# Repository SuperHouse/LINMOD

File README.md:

LINbus interface module
=======================
Copyright 2017 SuperHouse Automation Pty Ltd  www.superhouse.tv  

Simple serial interface breakout for LINbus. Includes an RJ45 connector
with the same pinout as AXA electric window motors.

Features:

 * MCP2003 LIN driver
 * Serial header matching FTDI pinout
 * RJ45 socket for LIN connection
 * DC jack to supply LINbus power

More information:

  http://www.superhouse.tv/linmod

INSTALLATION
------------
The design is saved as an EAGLE project. EAGLE PCB design software is
available from www.cadsoftusa.com free for non-commercial use. To use
this project download it and place the directory containing these files
into the "eagle" directory on your computer. Then open EAGLE and
navigate to the project.

CREDITS
-------
Designed by Jonathan Oxer jon@oxer.com.au

DISTRIBUTION
------------
The specific terms of distribution of this project are governed by the
license referenced below.

LICENSE
-------
Licensed under the TAPR Open Hardware License (www.tapr.org/OHL).
The "license" folder within this repository also contains a copy of
this license in plain text format.

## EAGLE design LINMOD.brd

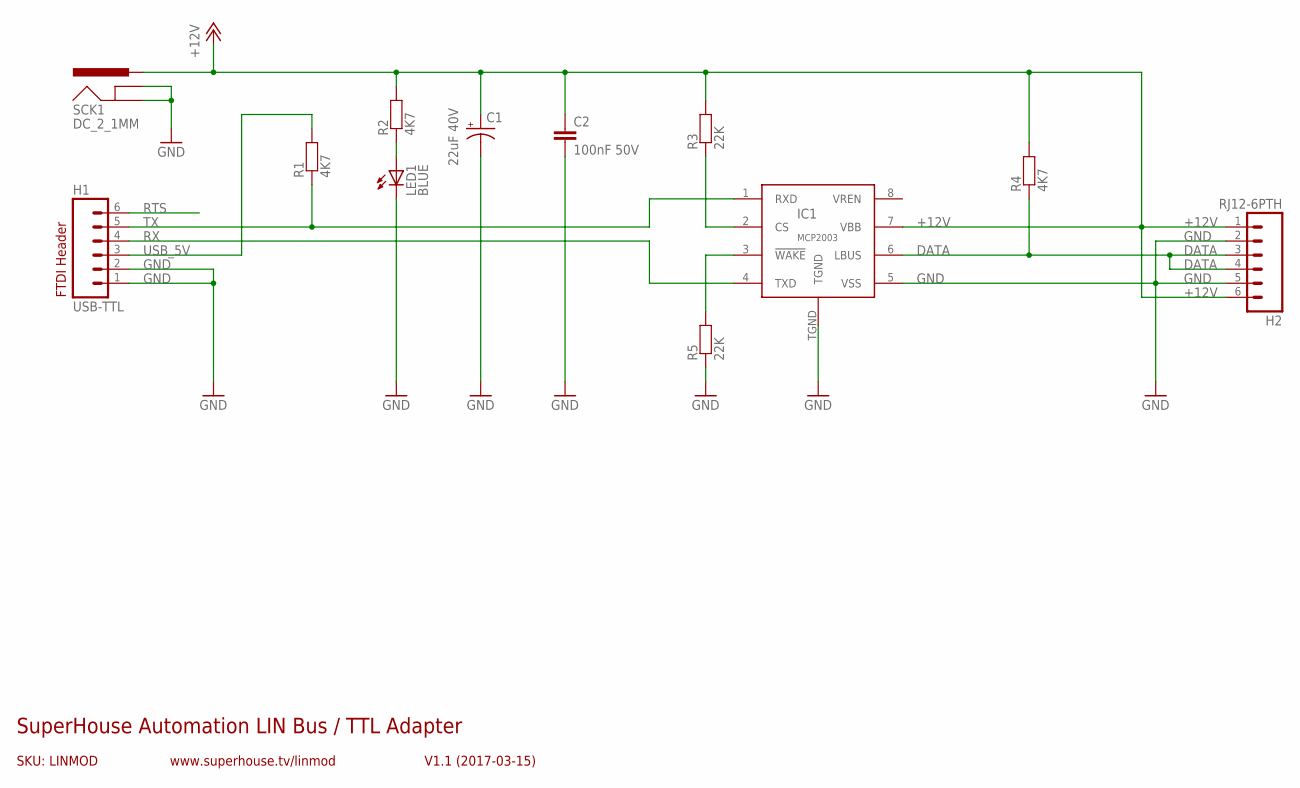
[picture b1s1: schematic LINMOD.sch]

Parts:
C1: 22uF 40V; UD-6,3X5,8_NICHICON
C2: 100nF 50V; 0603
H1: USB-TTL; 1X06
H2: RJ12-6PTH; RJ12-6
IC1: MCP2003; SOIC8T
LED1: BLUE; LED-0603
R1, R2, R4: 4K7; 0603
R3, R5: 22K; 0603
SCK1: DC_2_1MM; POWER_JACK_PTH

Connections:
+12V: C1.+, C2.1, H2.1, H2.6, IC1.7 (VBB), R2.2, R3.2, R4.2, SCK1.PWR
DATA: H2.3, H2.4, IC1.6 (LBUS), R4.1
GND: C1.-, C2.2, H1.1, H1.2, H2.2, H2.5, IC1.5 (VSS), IC1.TGND, LED1.C, R5.1, SCK1.GND, SCK1.GNDBREAK
unnamed: LED1.A, R2.1
unnamed: IC1.2 (CS), R3.1
unnamed: IC1.3 (!WAKE), R5.2
RTS: H1.6
RX: H1.4, IC1.4 (TXD)
TX: H1.5, IC1.1 (RXD), R1.1
USB_5V: H1.3, R1.2

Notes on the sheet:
FTDI Header
SKU: LINMOD
SuperHouse Automation LIN Bus / TTL Adapter
V1.1 (2017-03-15)
www.superhouse.tv/linmod

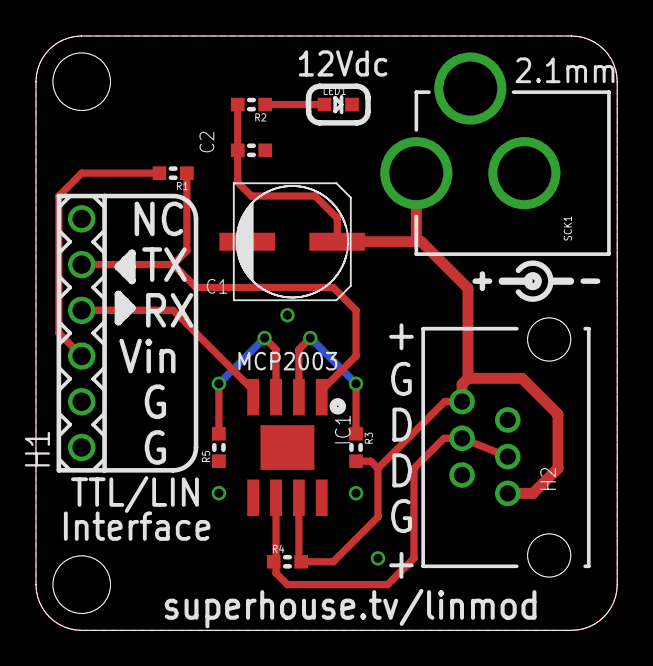
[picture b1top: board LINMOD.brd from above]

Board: 2 copper layers, 32.3 x 33.0 mm, 12 parts (0 on the bottom side), 9 nets.

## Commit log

2017-03-29 Initial import
2018-03-28 Added README and license files
2022-11-07 Added .gitignore.
